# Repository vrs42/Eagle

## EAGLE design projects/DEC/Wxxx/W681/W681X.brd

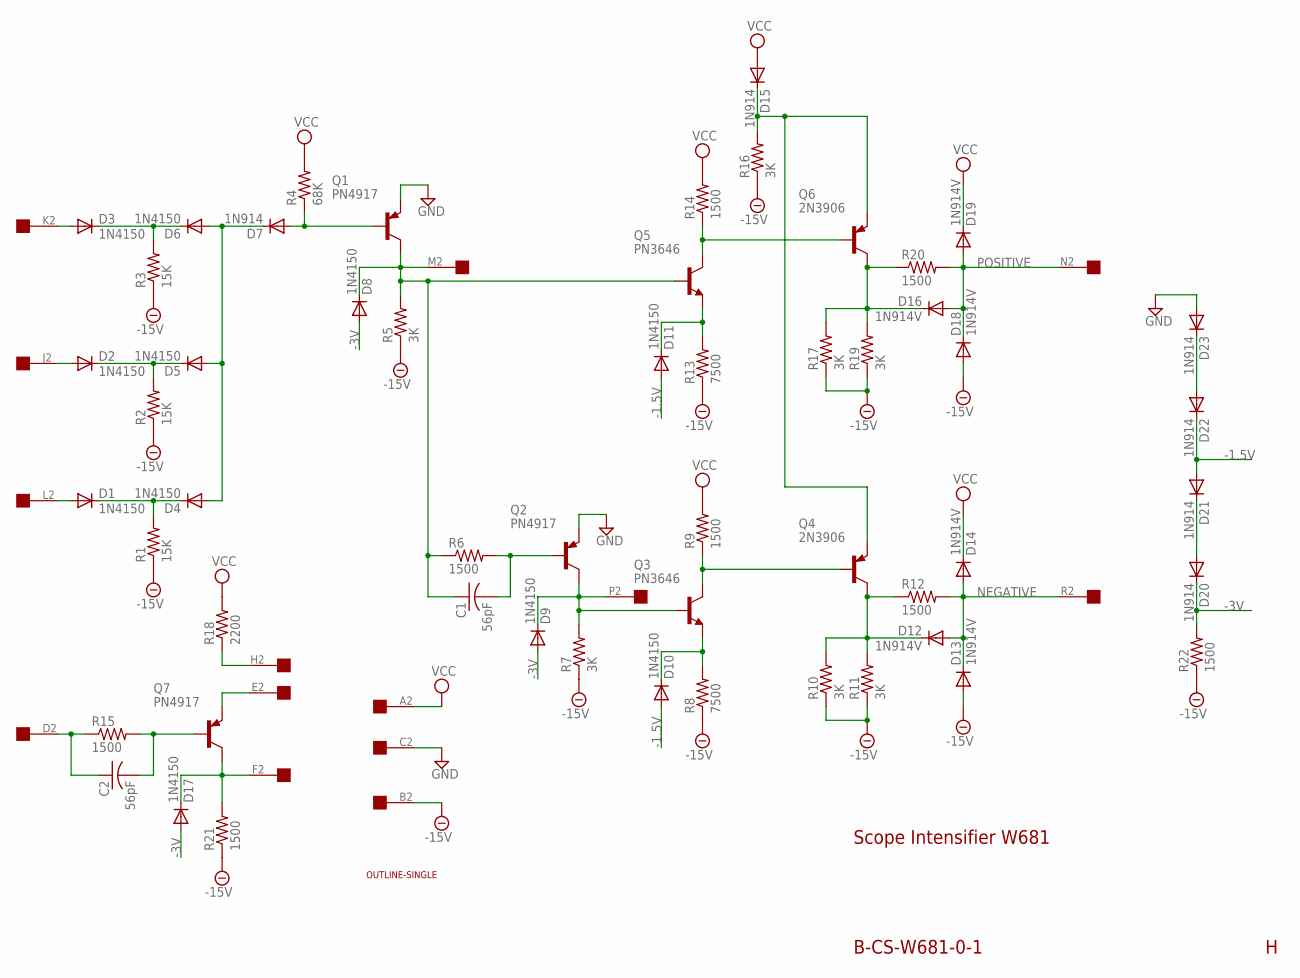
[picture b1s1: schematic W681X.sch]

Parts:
C1, C2: 56pF; C063-025X075
D1, D2, D3, D4, D5, D6, D8, D9, D10, D11, D17: 1N4150; DO35-10
D7, D15, D20, D21, D22, D23: 1N914; DO35-10
D12, D13, D14, D16, D18, D19: 1N914V; DO35-10
Q1, Q2, Q7: PN4917; TO5
Q3, Q5: PN3646; TO5
Q4, Q6: 2N3906; TO5
R1, R2, R3: 15K; 0207/10
R4: 68K; 0207/10
R5, R7, R10, R11, R16, R17, R19: 3K; 0207/10
R6, R9, R12, R14, R15, R20, R21, R22: 1500; 0207/10
R8, R13: 7500; 0207/10
R18: 2200; 0207/10
U$1: OUTLINE-SINGLE; SINGLE
U$2: EDGE-1; EDGE-CON1

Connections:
-1.5V: D10.A, D11.A, D21.A, D22.C
-3V: D8.A, D9.A, D17.A, D20.C, R22.2
-15V: D13.A, D18.A, R1.1, R2.1, R3.1, R5.1, R7.1, R8.1, R10.1, R11.1, R13.1, R16.1, R17.1, R19.1, R21.1, R22.1, U$2.B2
GND: D23.A, Q1.1 (E), Q2.1 (E), U$2.C2
unnamed: D1.A, U$2.L2
unnamed: D2.A, U$2.J2
unnamed: D3.A, U$2.K2
unnamed: D1.C, D4.C, R1.2
unnamed: D2.C, D5.C, R2.2
unnamed: D3.C, D6.C, R3.2
unnamed: D4.A, D5.A, D6.A, D7.C
unnamed: D7.A, Q1.2 (B), R4.1
unnamed: C1.1, D8.C, Q1.3 (C), Q5.2 (B), R5.2, R6.1, U$2.M2
unnamed: C1.2, Q2.2 (B), R6.2
unnamed: D9.C, Q2.3 (C), Q3.2 (B), R7.2, U$2.P2
unnamed: Q3.3 (C), Q4.2 (B), R9.1
unnamed: D10.C, Q3.1 (E), R8.2
unnamed: D12.C, Q4.3 (C), R10.2, R11.2, R12.1
unnamed: Q5.3 (C), Q6.2 (B), R14.1
unnamed: D11.C, Q5.1 (E), R13.2
unnamed: D15.C, Q4.1 (E), Q6.1 (E), R16.2
unnamed: D16.C, Q6.3 (C), R17.2, R19.2, R20.1
unnamed: C2.1, R15.1, U$2.D2
unnamed: C2.2, Q7.2 (B), R15.2
unnamed: D17.C, Q7.3 (C), R21.2, U$2.F2
unnamed: Q7.1 (E), U$2.E2
unnamed: R18.1, U$2.H2
unnamed: D20.A, D21.C
unnamed: D22.A, D23.C
NEGATIVE: D12.A, D13.C, D14.A, R12.2, U$2.R2
POSITIVE: D16.A, D18.C, D19.A, R20.2, U$2.N2
VCC: D14.C, D15.A, D19.C, R4.2, R9.2, R14.2, R18.2, U$2.A2

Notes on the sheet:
Scope Intensifier W681
B-CS-W681-0-1

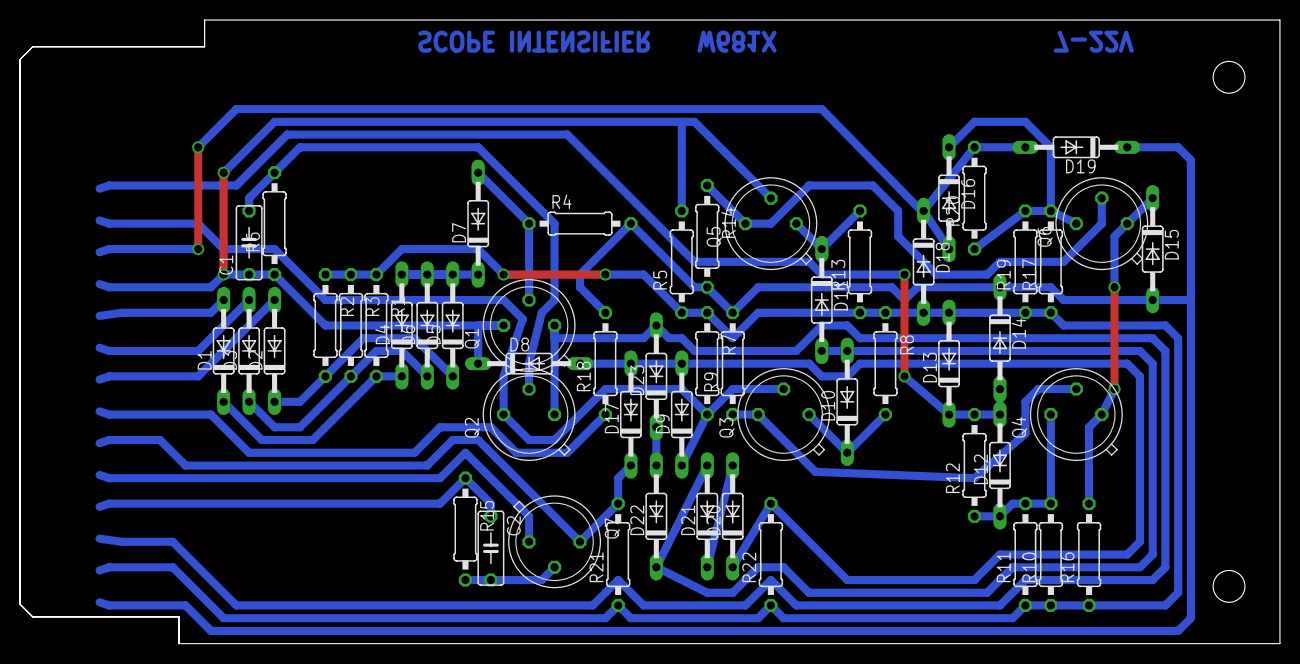
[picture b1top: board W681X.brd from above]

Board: 2 copper layers, 125.7 x 62.2 mm, 56 parts (0 on the bottom side), 32 nets.

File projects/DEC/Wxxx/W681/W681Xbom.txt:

Partlist exported from C:/Users/Vince/Documents/eagle/projects/DEC/Wxxx/W681/W681X.sch at 7/22/2017 2:01:49 PM

Qty Value          Device         Package      Parts                                         Description                                 
8   1500           R-US_0207/10   0207/10      R6, R9, R12, R14, R15, R20, R21, R22          RESISTOR, American symbol                   
3   15K            R-US_0207/10   0207/10      R1, R2, R3                                    RESISTOR, American symbol                   
11  1N4150         DIODE-DO35-10  DO35-10      D1, D2, D3, D4, D5, D6, D8, D9, D10, D11, D17 DIODE                                       
6   1N914          DIODE-DO35-10  DO35-10      D7, D15, D20, D21, D22, D23                   DIODE                                       
6   1N914V         DIODE-DO35-10  DO35-10      D12, D13, D14, D16, D18, D19                  DIODE                                       
1   2200           R-US_0207/10   0207/10      R18                                           RESISTOR, American symbol                   
2   2N3906         -PNP-TO5       TO5          Q4, Q6                                        PNP Transistror                             
7   3K             R-US_0207/10   0207/10      R5, R7, R10, R11, R16, R17, R19               RESISTOR, American symbol                   
2   56pF           C-US           C063-025X075 C1, C2                                        Capacitors with funky DEC lead spacing.     
1   68K            R-US_0207/10   0207/10      R4                                            RESISTOR, American symbol                   
2   7500           R-US_0207/10   0207/10      R8, R13                                       RESISTOR, American symbol                   
1   OUTLINE-SINGLE OUTLINE-SINGLE SINGLE       U$1                                           W681 Board.              
2   PN3646         -NPN-TO5       TO5          Q3, Q5                                        NPN Transistror                             
3   PN4917         -PNP-TO5       TO5          Q1, Q2, Q7                                    PNP Transistror

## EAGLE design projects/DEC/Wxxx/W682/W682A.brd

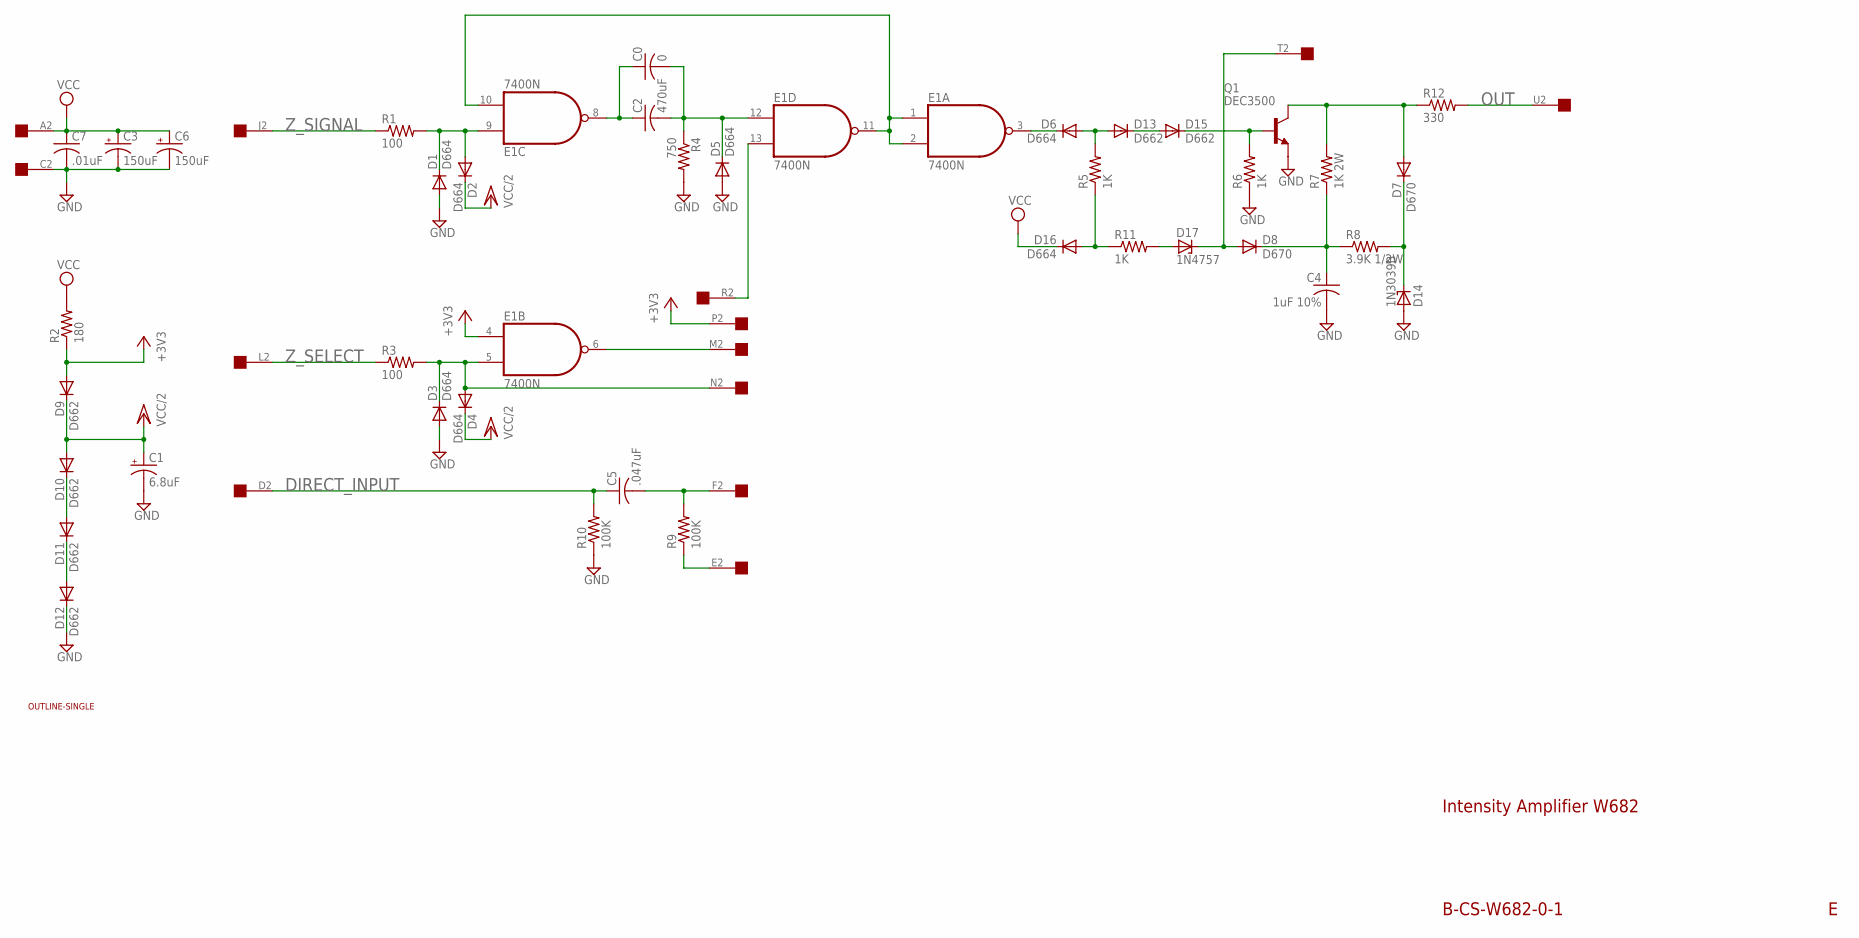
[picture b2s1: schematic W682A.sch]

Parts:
C0: 0; C050-025X075
C1: 6.8uF; E12-8
C2: 470uF; C050-025X075
C3, C6: 150uF; E22-9
C4: 1uF 10%; C325-137X374
C5: .047uF; C275-093X316
C7: .01uF; C050-025X075
D1, D2, D3, D4, D5, D6, D16: D664; DO35-10
D7, D8: D670; DO41-10
D9, D10, D11, D12, D13, D15: D662; DO35-10
D14: 1N3039B; ZDIO12.5
D17: 1N4757; ZDIO12.5
E1: 7400N; DIL14
Q1: DEC3500; TO39
R1, R3: 100; 0207/10
R2: 180; 0207/10
R4: 750; 0207/10
R5, R6, R11: 1K; 0207/10
R7: 1K 2W; 0818/25
R8: 3.9K 1/2W; 0411/15
R9, R10: 100K; 0207/10
R12: 330; 0207/10
U$1: OUTLINE-SINGLE; SINGLE
U$2: EDGE-1; EDGE-CON1

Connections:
+3V3: D9.A, E1.4 (I0), R2.1, U$2.P2
DIRECT_INPUT: C5.1, R10.2, U$2.D2
GND: C1.-, C3.-, C4.2, C6.-, C7.2, D1.A, D3.A, D5.A, D12.C, D14.A, E1.7 (GND), Q1.1 (E), R4.2, R6.1, R10.1, U$2.C2
unnamed: E1.13 (I1), U$2.R2
unnamed: D1.C, D2.A, E1.9 (I0), R1.2
unnamed: E1.1 (I0), E1.2 (I1), E1.10 (I1), E1.11 (O)
unnamed: C0.2, C2.2, D5.C, E1.12 (I0), R4.1
unnamed: C0.1, C2.1, E1.8 (O)
unnamed: D3.C, D4.A, E1.5 (I1), R3.2, U$2.N2
unnamed: D11.C, D12.A
unnamed: D10.C, D11.A
unnamed: E1.6 (O), U$2.M2
unnamed: C5.2, R9.2, U$2.F2
unnamed: R9.1, U$2.E2
unnamed: D16.A, R5.1, R11.1
unnamed: C4.1, D8.C, R7.1, R8.1
unnamed: D7.A, Q1.3 (C), R7.2, R12.1
unnamed: D7.C, D14.C, R8.2
unnamed: D6.C, E1.3 (O)
unnamed: D6.A, D13.A, R5.2
unnamed: D17.A, R11.2
unnamed: D8.A, D17.C, U$2.T2
unnamed: D15.C, Q1.2 (B), R6.2
unnamed: D13.C, D15.A
OUT: R12.2, U$2.U2
VCC: C3.+, C6.+, C7.1, D16.C, E1.14 (VCC), R2.2, U$2.A2
VCC/2: C1.+, D2.C, D4.C, D9.C, D10.A
Z_SELECT: R3.1, U$2.L2
Z_SIGNAL: R1.1, U$2.J2

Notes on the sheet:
B-CS-W682-0-1
Intensity Amplifier W682

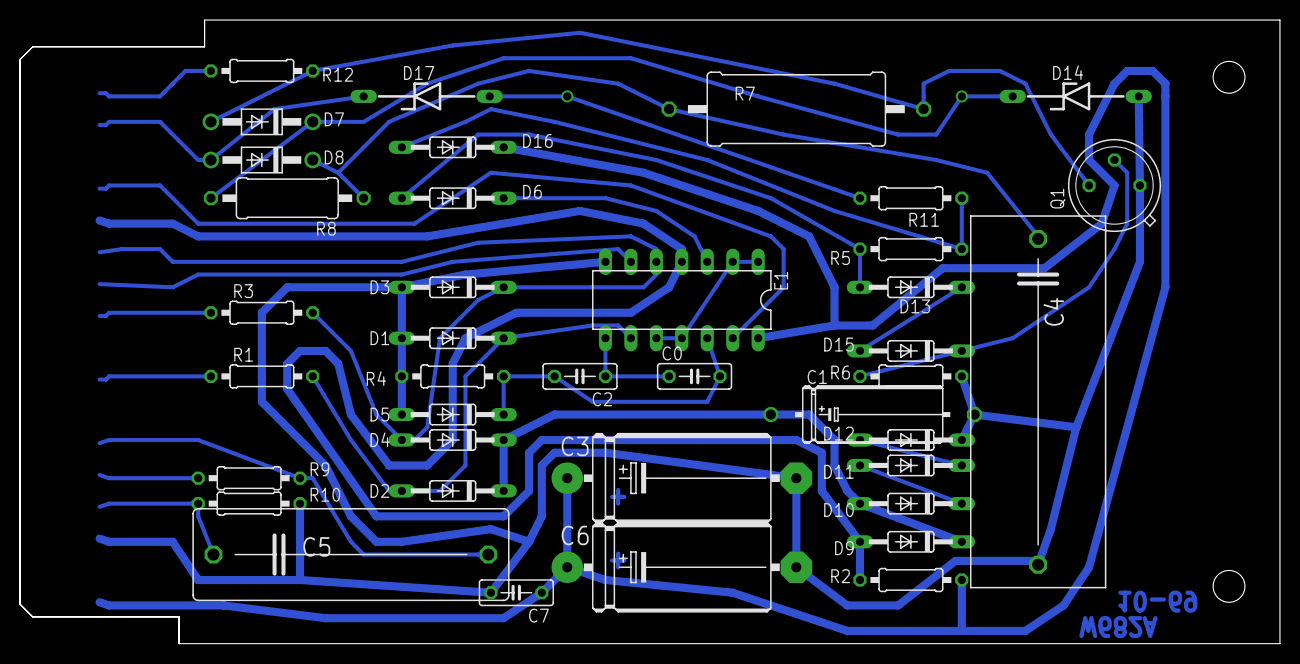
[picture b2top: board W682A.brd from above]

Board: 2 copper layers, 125.7 x 62.2 mm, 41 parts (0 on the bottom side), 29 nets.

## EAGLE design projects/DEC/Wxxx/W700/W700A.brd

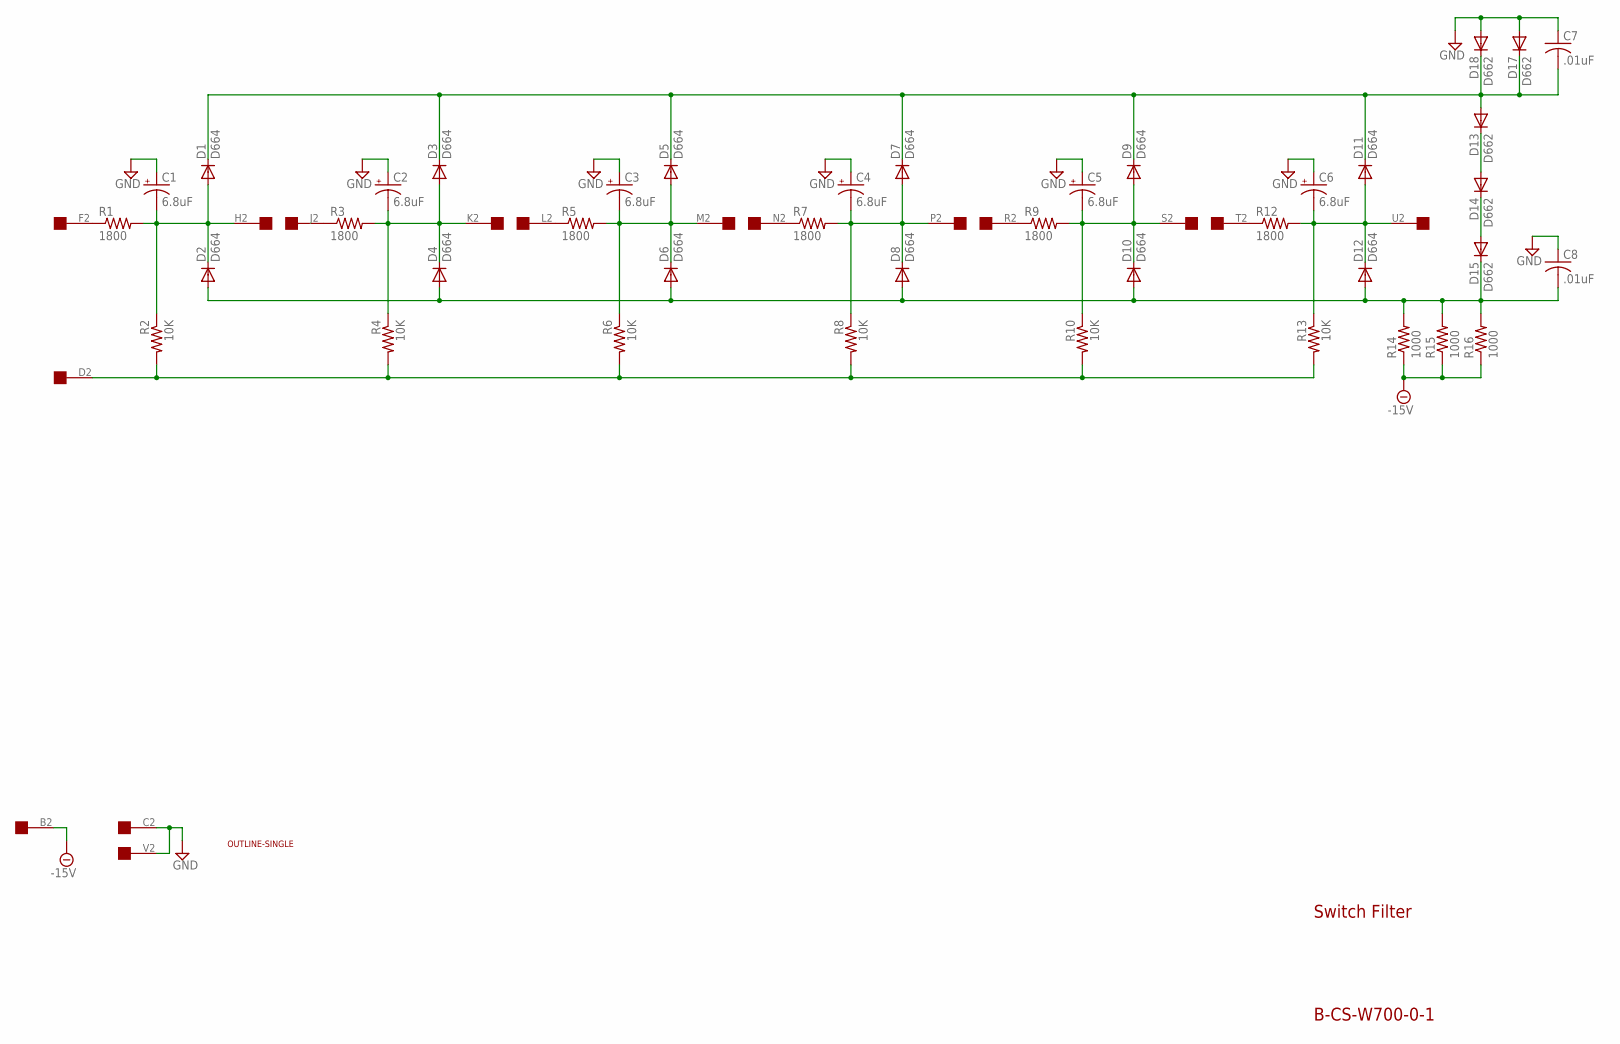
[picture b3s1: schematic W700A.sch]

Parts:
C1, C2, C3, C4, C5, C6: 6.8uF; E15-5
C7, C8: .01uF; C050-025X075
D1, D2, D3, D4, D5, D6, D7, D8, D9, D10, D11, D12: D664; DO35-10
D13, D14, D15, D17, D18: D662; DO35-10
R1, R3, R5, R7, R9, R12: 1800; 0207/10
R2, R4, R6, R8, R10, R13: 10K; 0207/10
R14, R15, R16: 1000; 0207/10
U$1: OUTLINE-SINGLE; SINGLE
U$3: EDGE-1; EDGE-CON1

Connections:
-15V: R14.1, R15.1, R16.1, U$3.B2
D2: R2.2, R4.2, R6.2, R8.2, R10.2, R13.2, U$3.D2
F2: R1.1, U$3.F2
GND: C1.+, C2.+, C3.+, C4.+, C5.+, C6.+, C7.1, C8.1, D17.A, D18.A, U$3.C2, U$3.V2
H2: C1.-, D1.A, D2.C, R1.2, R2.1, U$3.H2
J2: R3.1, U$3.J2
K2: C2.-, D3.A, D4.C, R3.2, R4.1, U$3.K2
L2: R5.1, U$3.L2
unnamed: C8.2, D2.A, D4.A, D6.A, D8.A, D10.A, D12.A, D15.C, R14.2, R15.2, R16.2
unnamed: R7.1, U$3.N2
unnamed: C3.-, D5.A, D6.C, R5.2, R6.1, U$3.M2
unnamed: C7.2, D1.C, D3.C, D5.C, D7.C, D9.C, D11.C, D13.A, D17.C, D18.C
unnamed: D14.C, D15.A
unnamed: D13.C, D14.A
P2: C4.-, D7.A, D8.C, R7.2, R8.1, U$3.P2
R2: R9.1, U$3.R2
S2: C5.-, D9.A, D10.C, R9.2, R10.1, U$3.S2
T2: R12.1, U$3.T2
U2: C6.-, D11.A, D12.C, R12.2, R13.1, U$3.U2

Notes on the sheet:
Switch Filter
B-CS-W700-0-1

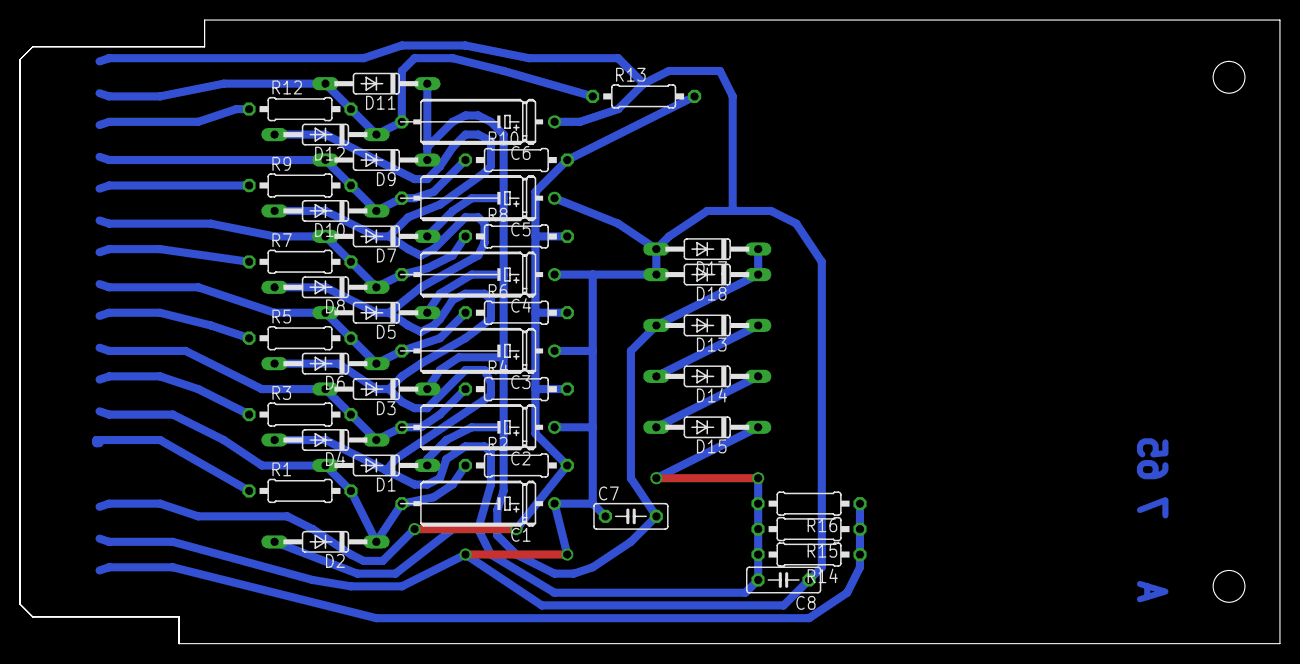
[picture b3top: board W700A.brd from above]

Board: 2 copper layers, 125.7 x 62.2 mm, 42 parts (0 on the bottom side), 19 nets.

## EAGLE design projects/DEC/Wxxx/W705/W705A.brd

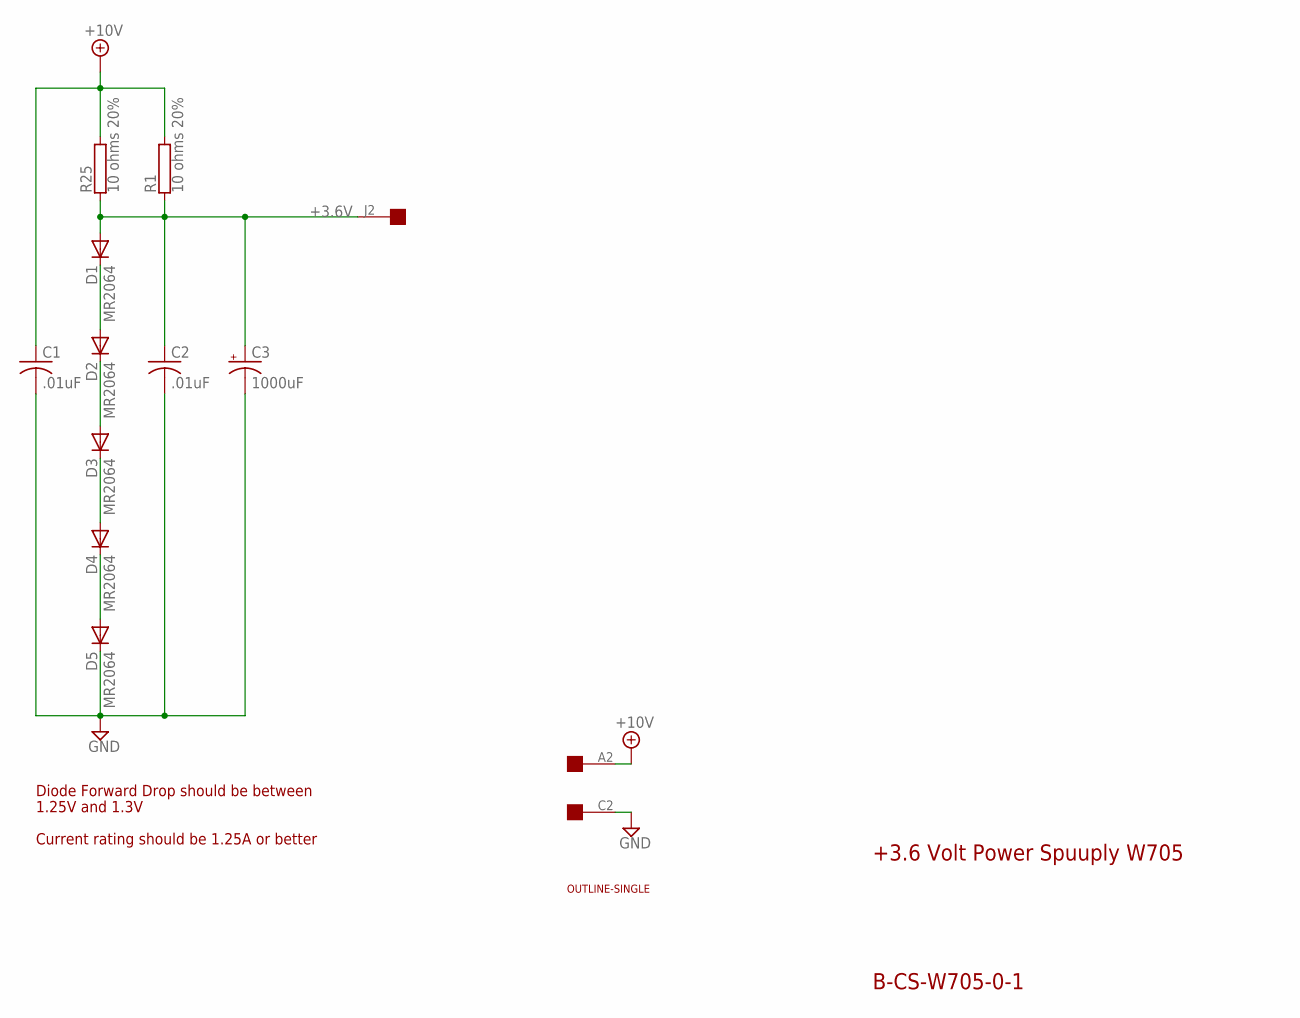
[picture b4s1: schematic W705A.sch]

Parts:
C1, C2: .01uF; C050-025X075
C3: 1000uF; E55-25
D1, D2, D3, D4, D5: MR2064; DO41-10
R1, R25: 10 ohms 20%; KH216-8
U$1: OUTLINE-SINGLE; SINGLE
U$2: EDGE-1; EDGE-CON1

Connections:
+3.6V: C2.1, C3.+, D1.A, R1.1, R25.1, U$2.J2
+10V: C1.1, R1.2, R25.2, U$2.A2
GND: C1.2, C2.2, C3.-, D5.C, U$2.C2
unnamed: D1.C, D2.A
unnamed: D2.C, D3.A
unnamed: D4.C, D5.A
unnamed: D3.C, D4.A

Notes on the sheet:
+3.6 Volt Power Spuuply W705
B-CS-W705-0-1
Diode Forward Drop should be between
1.25V and 1.3V
Current rating should be 1.25A or better

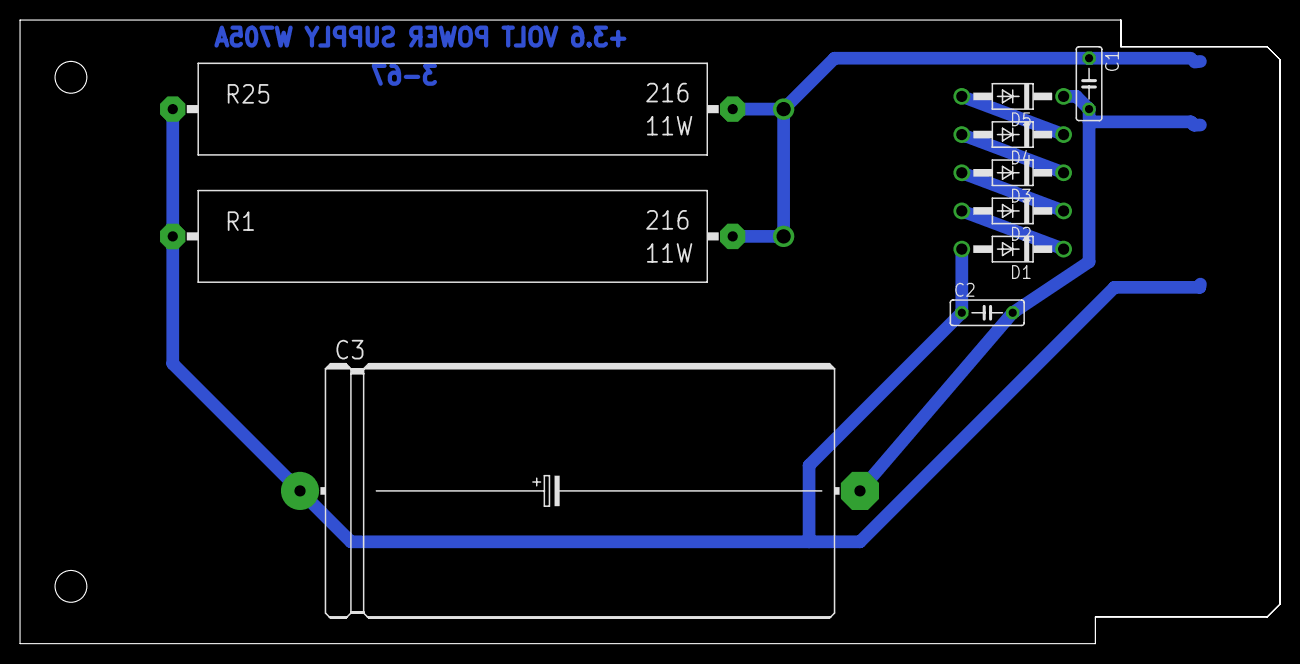
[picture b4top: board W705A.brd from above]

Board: 2 copper layers, 125.7 x 62.2 mm, 12 parts (0 on the bottom side), 7 nets.
